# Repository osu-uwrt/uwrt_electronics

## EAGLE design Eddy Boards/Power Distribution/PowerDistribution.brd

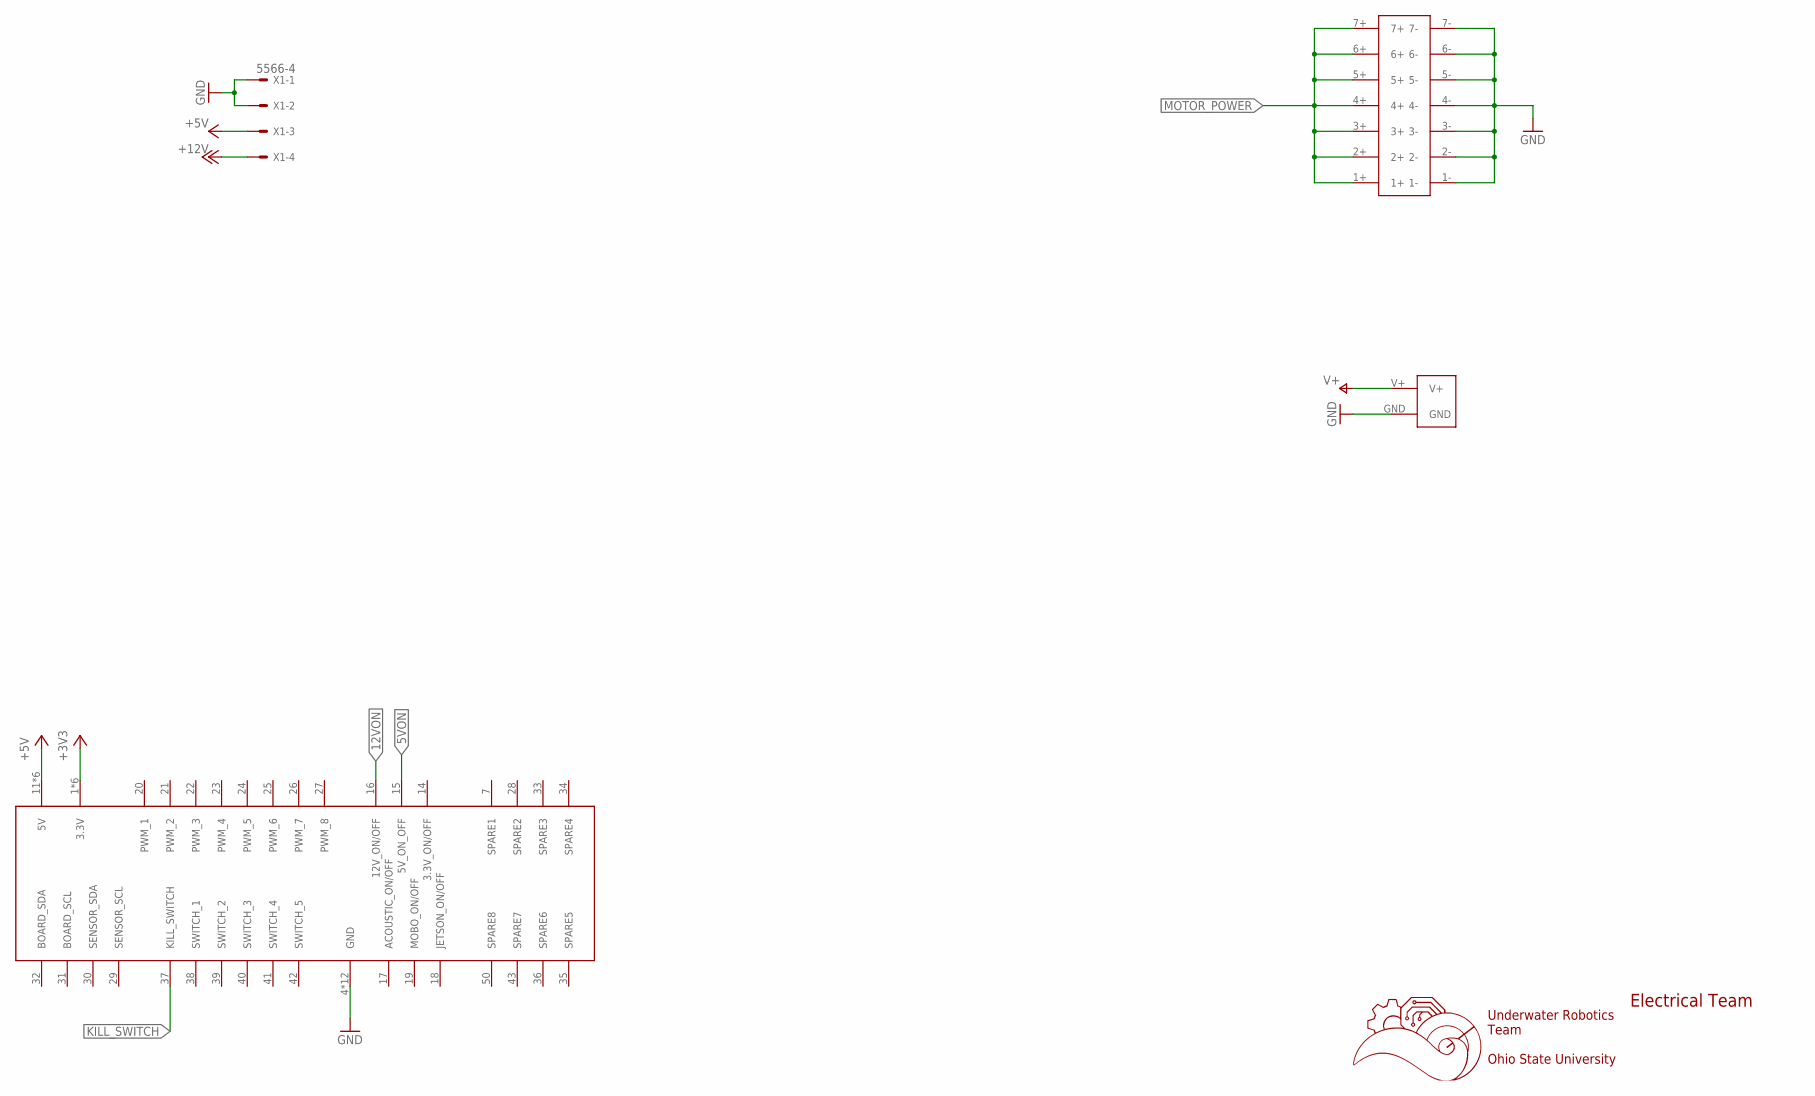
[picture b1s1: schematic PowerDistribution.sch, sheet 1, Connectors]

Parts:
U$1: 5530843-EDGE; 5530843-6-BOARDFINGERS
U$2: XT90PWH
U$4: 14PIN-VERT; 14PIN_VERT
X1: 5566-4

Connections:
5VON: U$1.15 (5V_ON_OFF); also elsewhere on the board
12VON: U$1.16 (12V_ON/OFF); also elsewhere on the board
+3V3: U$1.1 (3.3V), U$1.2 (3.3V), U$1.3 (3.3V), U$1.54 (3.3V), U$1.55 (3.3V), U$1.56 (3.3V); also elsewhere on the board
+5V: U$1.11 (5V), U$1.12 (5V), U$1.13 (5V), U$1.44 (5V), U$1.45 (5V), U$1.46 (5V), X1.3; also elsewhere on the board
+12V: X1.4; also elsewhere on the board
GND: U$1.4 (GND), U$1.5 (GND), U$1.6 (GND), U$1.8 (GND), U$1.9 (GND), U$1.10 (GND), U$1.47 (GND), U$1.48 (GND), U$1.49 (GND), U$1.51 (GND), U$1.52 (GND), U$1.53 (GND), U$2.GND, U$4.1-, U$4.2-, U$4.3-, U$4.4-, U$4.5-, U$4.6-, U$4.7-, X1.1, X1.2; also elsewhere on the board
KILL_SWITCH: U$1.37 (KILL_SWITCH); also elsewhere on the board
MOTOR_POWER: U$4.1+, U$4.2+, U$4.3+, U$4.4+, U$4.5+, U$4.6+, U$4.7+; also elsewhere on the board
V+: U$2.V+; also elsewhere on the board

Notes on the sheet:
Underwater Robotics Team Ohio State University
Electrical Team

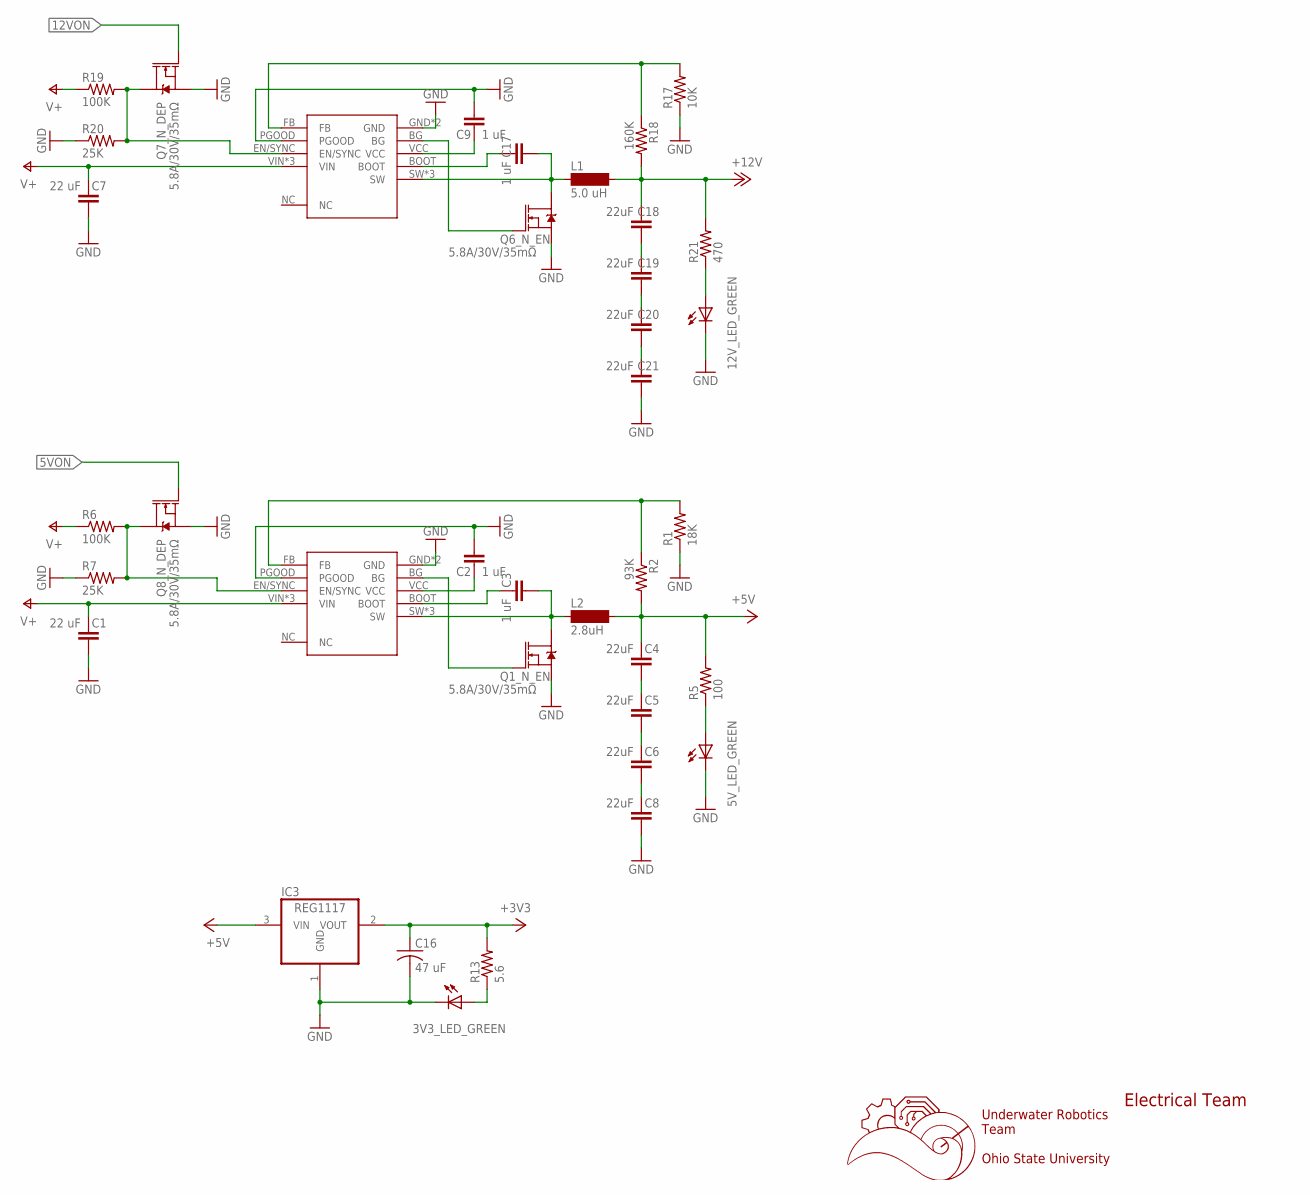
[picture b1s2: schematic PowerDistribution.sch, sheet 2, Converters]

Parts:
3V3_LED_GREEN, 5V_LED_GREEN, 12V_LED_GREEN: LEDCHIPLED_0603; CHIPLED_0603
C1, C7: 22 uF; C0603
C2, C3, C9, C17: 1 uF; C0603
C4, C5, C6, C8, C18, C19, C20, C21: 22uF; C0603
C16: 47 uF; C1206K
IC3: REG1117; SOT223
L1: 5.0 uH; MS85
L2: 2.8uH; MS85
Q1_N_EN, Q6_N_EN, Q7_N_DEP, Q8_N_DEP: 5.8A/30V/35mΩ; SOT23-3
R1: 18K; R0603
R2: 93K; R0603
R5: 100; R0603
R6, R19: 100K; R0603
R7, R20: 25K; R0603
R13: 5.6; R0603
R17: 10K; R0603
R18: 160K; R0603
R21: 470; R0603
U$3, U$6: RT7258-2

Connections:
5VEN: Q8_N_DEP.3 (D), R6.2, R7.2, U$3.EN/SYNC
5VON: Q8_N_DEP.1 (G); also elsewhere on the board
12EN: Q7_N_DEP.3 (D), R19.2, R20.2, U$6.EN/SYNC
12VON: Q7_N_DEP.1 (G); also elsewhere on the board
+3V3: C16.1, IC3.2 (VOUT), R13.2; also elsewhere on the board
+5V: C4.2, IC3.3 (VIN), L2.2, R2.2, R5.2; also elsewhere on the board
+12V: C18.2, L1.2, R18.2, R21.2; also elsewhere on the board
BG: Q1_N_EN.1 (G), U$3.BG
BG2: Q6_N_EN.1 (G), U$6.BG
GND: 3V3_LED_GREEN.C, 5V_LED_GREEN.C, 12V_LED_GREEN.C, C1.1, C2.1, C7.1, C8.1, C9.1, C16.2, C21.1, IC3.1 (GND), Q1_N_EN.2 (S), Q6_N_EN.2 (S), Q7_N_DEP.2 (S), Q8_N_DEP.2 (S), R1.1, R7.1, R17.1, R20.1, U$3.GND, U$3.GND2 (GND), U$3.PGOOD, U$6.GND, U$6.GND2 (GND), U$6.PGOOD; also elsewhere on the board
unnamed: C2.2, U$3.VCC
unnamed: C3.2, U$3.BOOT
unnamed: C5.1, C6.2
unnamed: C6.1, C8.2
unnamed: C4.1, C5.2
unnamed: R1.2, R2.1, U$3.FB
unnamed: 5V_LED_GREEN.A, R5.1
unnamed: C9.2, U$6.VCC
unnamed: 12V_LED_GREEN.A, R21.1
unnamed: C17.2, U$6.BOOT
unnamed: C19.1, C20.2
unnamed: C20.1, C21.2
unnamed: C18.1, C19.2
unnamed: R17.2, R18.1, U$6.FB
unnamed: 3V3_LED_GREEN.A, R13.1
V+: C1.2, C7.2, R6.1, R19.1, U$3.VIN, U$3.VIN2 (VIN), U$3.VIN3 (VIN), U$6.VIN, U$6.VIN2 (VIN), U$6.VIN3 (VIN); also elsewhere on the board
V+1: C17.1, L1.1, Q6_N_EN.3 (D), U$6.SW, U$6.SW2 (SW), U$6.SW3 (SW)
V+2: C3.1, L2.1, Q1_N_EN.3 (D), U$3.SW, U$3.SW2 (SW), U$3.SW3 (SW)

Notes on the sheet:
Underwater Robotics Team Ohio State University
Electrical Team

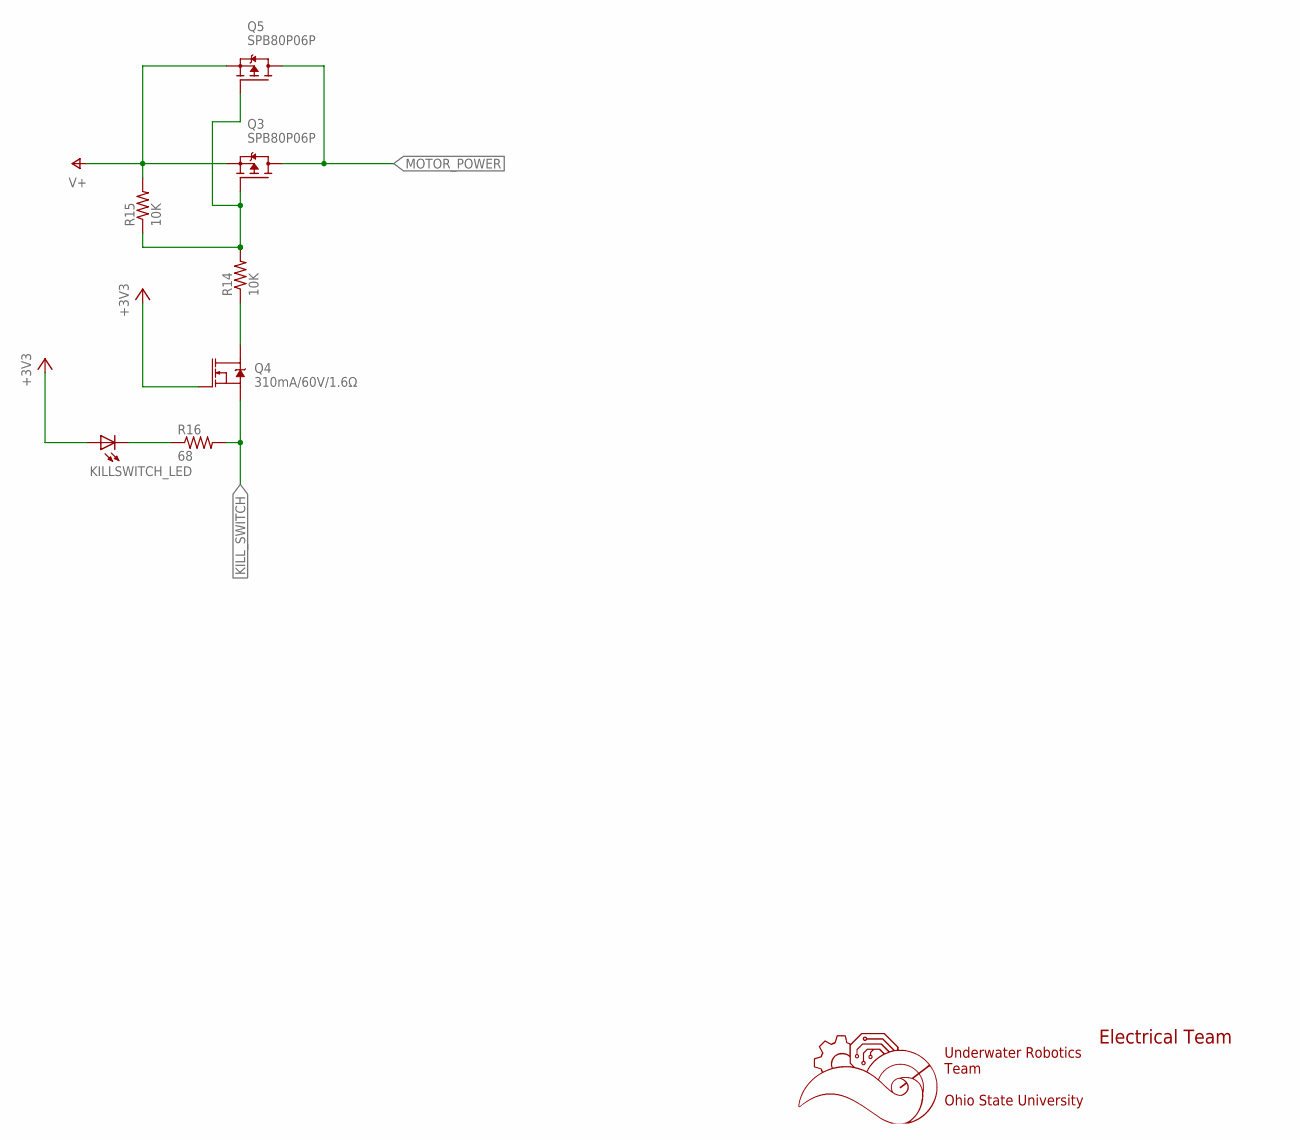
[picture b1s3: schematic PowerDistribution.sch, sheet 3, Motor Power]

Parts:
KILLSWITCH_LED: LEDCHIP-LED0603; CHIP-LED0603
Q3, Q5: SPB80P06P; TO263
Q4: 310mA/60V/1.6Ω; SOT323
R14, R15: 10K; R0603
R16: 68; R0603

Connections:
+3V3: KILLSWITCH_LED.A, Q4.1 (G); also elsewhere on the board
KILL_SWITCH: Q4.2 (S), R16.2; also elsewhere on the board
MOTOR_POWER: Q3.3 (D), Q5.3 (D); also elsewhere on the board
unnamed: Q4.3 (D), R14.1
unnamed: Q3.1 (G), Q5.1 (G), R14.2, R15.1
unnamed: KILLSWITCH_LED.C, R16.1
V+: Q3.2 (S), Q5.2 (S), R15.2; also elsewhere on the board

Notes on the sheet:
Underwater Robotics Team Ohio State University
Electrical Team

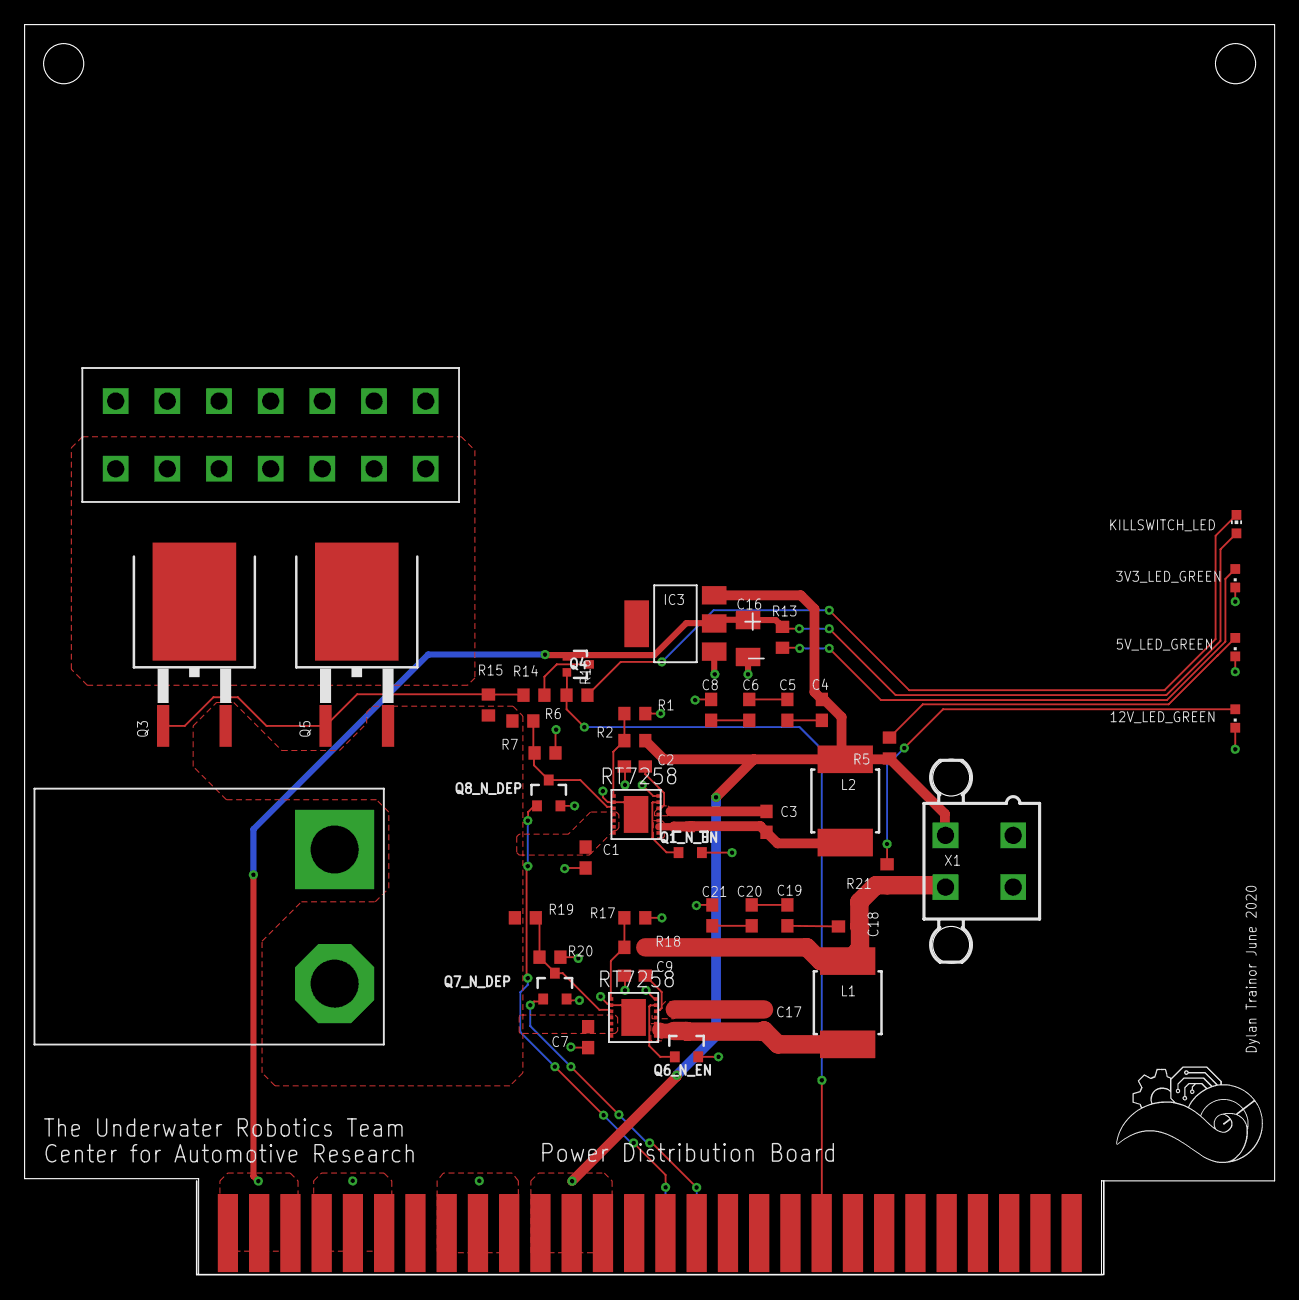
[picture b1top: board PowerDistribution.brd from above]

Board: 2 copper layers, 101.6 x 101.6 mm, 49 parts (0 on the bottom side), 33 nets.

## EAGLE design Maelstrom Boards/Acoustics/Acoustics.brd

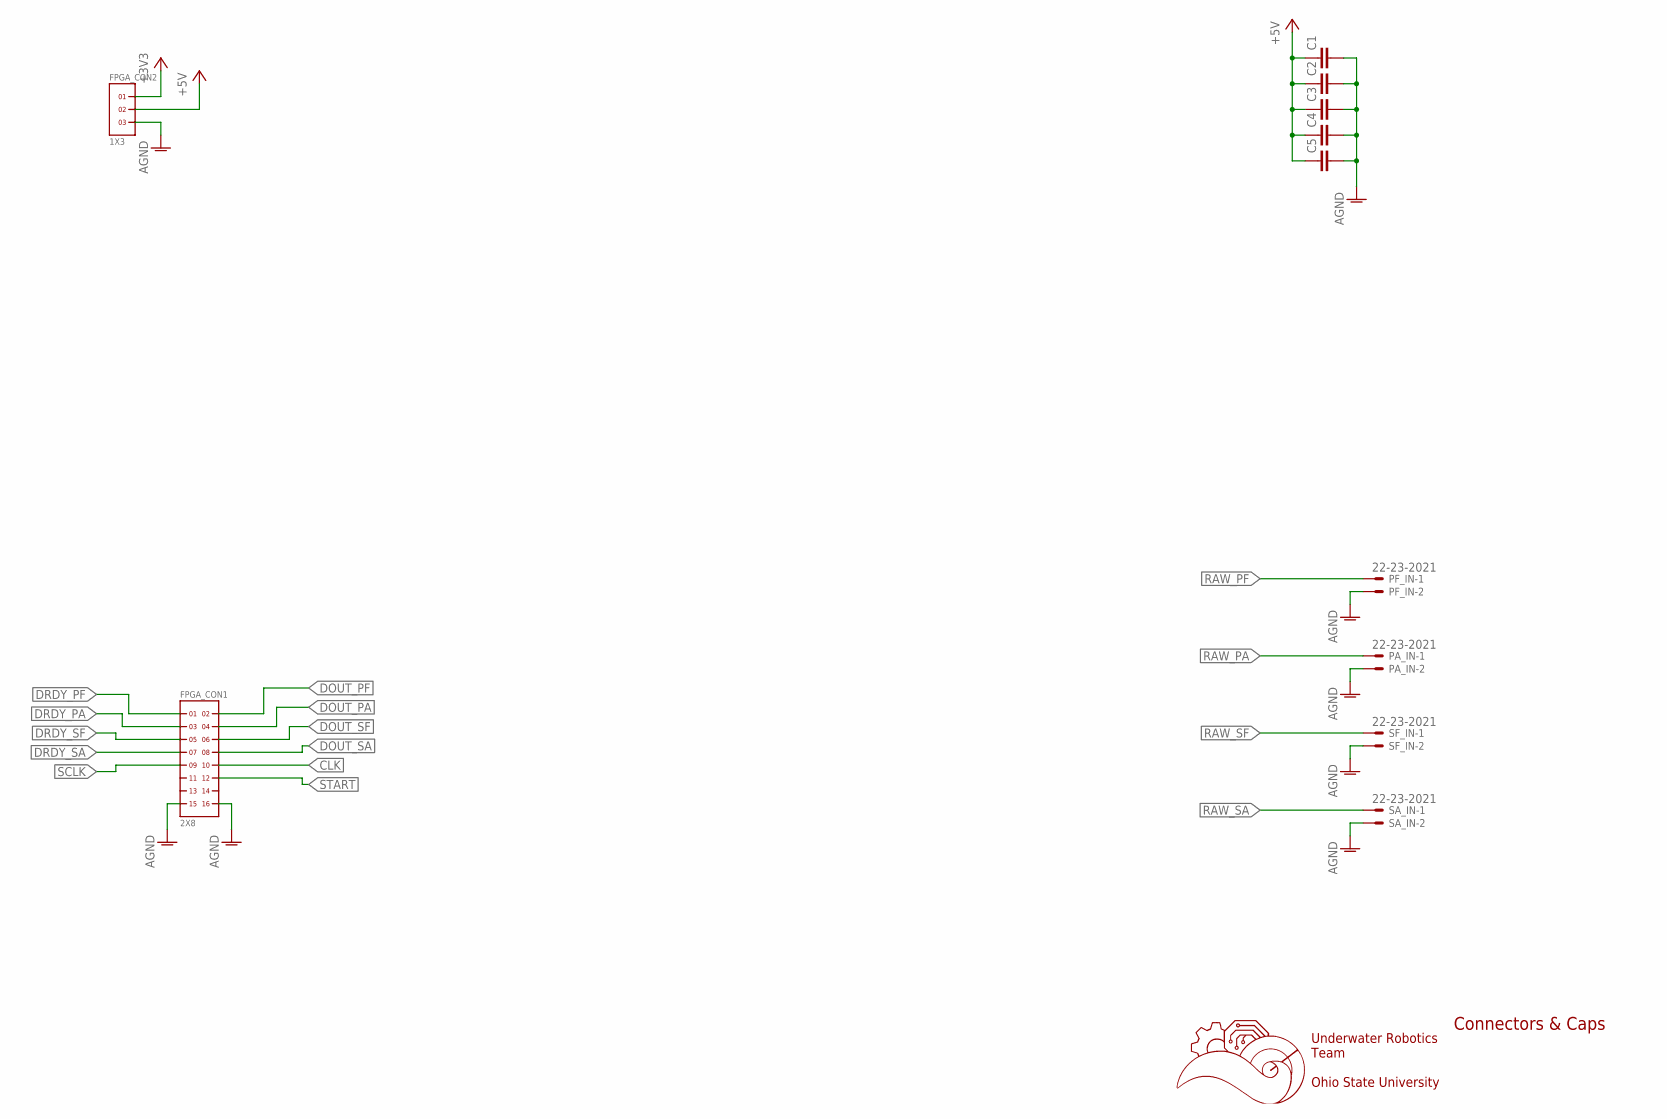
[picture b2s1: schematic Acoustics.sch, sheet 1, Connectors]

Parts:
C1, C2, C3, C4, C5: C2,5-3; C2.5-3
FPGA_CON1: 2X8
FPGA_CON2: 1X3
PA_IN: 22-23-2021
PF_IN: 22-23-2021
SA_IN: 22-23-2021
SF_IN: 22-23-2021

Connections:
+3V3: FPGA_CON2.1; also elsewhere on the board
+5V: C1.1, C2.1, C3.1, C4.1, C5.1, FPGA_CON2.2
CLK: FPGA_CON1.10; also elsewhere on the board
DOUT_PA: FPGA_CON1.4; also elsewhere on the board
DOUT_PF: FPGA_CON1.2; also elsewhere on the board
DOUT_SA: FPGA_CON1.8; also elsewhere on the board
DOUT_SF: FPGA_CON1.6; also elsewhere on the board
DRDY_PA: FPGA_CON1.3; also elsewhere on the board
DRDY_PF: FPGA_CON1.1; also elsewhere on the board
DRDY_SA: FPGA_CON1.7; also elsewhere on the board
DRDY_SF: FPGA_CON1.5; also elsewhere on the board
GND: C1.2, C2.2, C3.2, C4.2, C5.2, FPGA_CON1.15, FPGA_CON1.16, FPGA_CON2.3, PA_IN.2, PF_IN.2, SA_IN.2, SF_IN.2; also elsewhere on the board
RAW_PA: PA_IN.1; also elsewhere on the board
RAW_PF: PF_IN.1; also elsewhere on the board
RAW_SA: SA_IN.1; also elsewhere on the board
RAW_SF: SF_IN.1; also elsewhere on the board
SCLK: FPGA_CON1.9; also elsewhere on the board
START: FPGA_CON1.12; also elsewhere on the board

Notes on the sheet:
Underwater Robotics Team Ohio State University
Connectors & Caps

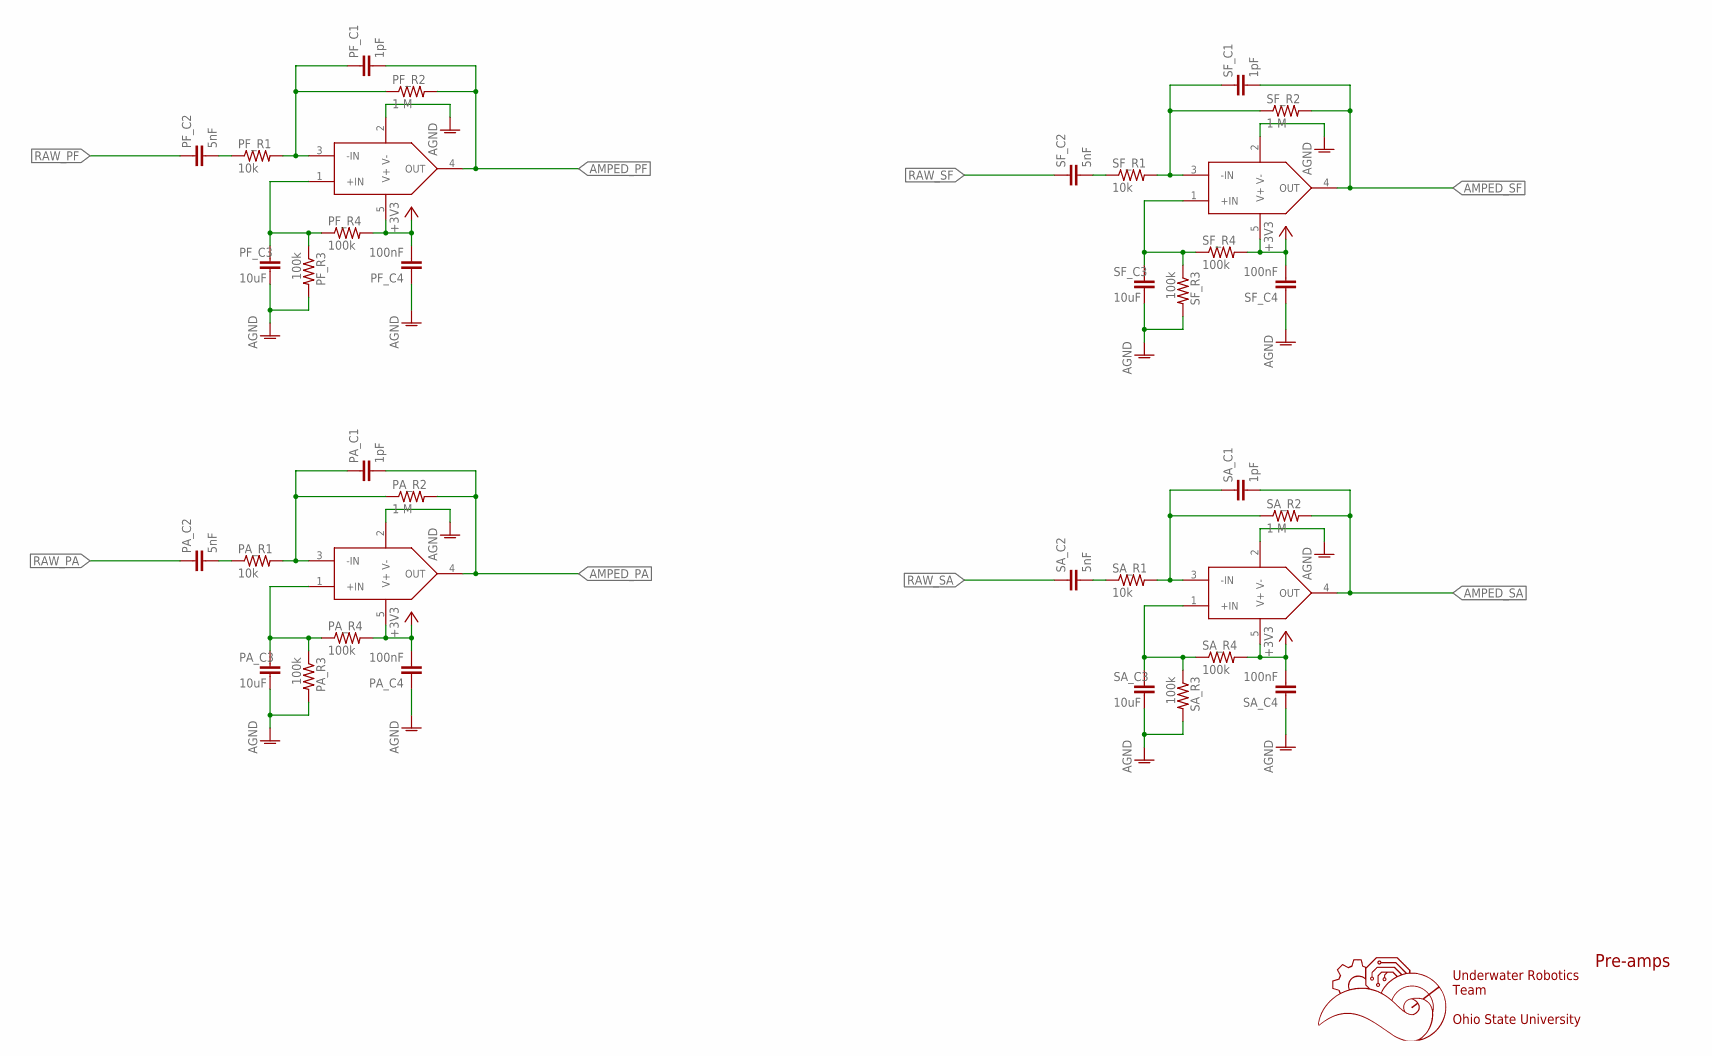
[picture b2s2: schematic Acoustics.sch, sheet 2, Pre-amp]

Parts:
H4_PREAMP4: TLV6741; SC70-5
PA_C1: 1pF; C0603
PA_C2: 5nF; C0603
PA_C3: 10uF; C0603
PA_C4: 100nF; C0603
PA_PREAMP: TLV6741; SC70-5
PA_R1: 10k; R0603
PA_R2: 1 M; R0603
PA_R3, PA_R4: 100k; R0603
PF_C1: 1pF; C0603
PF_C2: 5nF; C0603
PF_C3: 10uF; C0603
PF_C4: 100nF; C0603
PF_PREAMP: TLV6741; SC70-5
PF_R1: 10k; R0603
PF_R2: 1 M; R0603
PF_R3, PF_R4: 100k; R0603
SA_C1: 1pF; C0603
SA_C2: 5nF; C0603
SA_C3: 10uF; C0603
SA_C4: 100nF; C0603
SA_R1: 10k; R0603
SA_R2: 1 M; R0603
SA_R3, SA_R4: 100k; R0603
SF_C1: 1pF; C0603
SF_C2: 5nF; C0603
SF_C3: 10uF; C0603
SF_C4: 100nF; C0603
SF_PREAMP3: TLV6741; SC70-5
SF_R1: 10k; R0603
SF_R2: 1 M; R0603
SF_R3, SF_R4: 100k; R0603

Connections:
+3V3: H4_PREAMP4.5 (V+), PA_C4.2, PA_PREAMP.5 (V+), PA_R4.2, PF_C4.2, PF_PREAMP.5 (V+), PF_R4.2, SA_C4.2, SA_R4.2, SF_C4.2, SF_PREAMP3.5 (V+), SF_R4.2; also elsewhere on the board
AMPED_PA: PA_C1.2, PA_PREAMP.4 (OUT), PA_R2.2; also elsewhere on the board
AMPED_PF: PF_C1.2, PF_PREAMP.4 (OUT), PF_R2.2; also elsewhere on the board
AMPED_SA: H4_PREAMP4.4 (OUT), SA_C1.2, SA_R2.2; also elsewhere on the board
AMPED_SF: SF_C1.2, SF_PREAMP3.4 (OUT), SF_R2.2; also elsewhere on the board
GND: H4_PREAMP4.2 (V-), PA_C3.2, PA_C4.1, PA_PREAMP.2 (V-), PA_R3.2, PF_C3.2, PF_C4.1, PF_PREAMP.2 (V-), PF_R3.2, SA_C3.2, SA_C4.1, SA_R3.2, SF_C3.2, SF_C4.1, SF_PREAMP3.2 (V-), SF_R3.2; also elsewhere on the board
unnamed: PF_C2.2, PF_R1.1
unnamed: PF_C1.1, PF_PREAMP.3 (-IN), PF_R1.2, PF_R2.1
unnamed: PF_C3.1, PF_PREAMP.1 (+IN), PF_R3.1, PF_R4.1
unnamed: PA_C2.2, PA_R1.1
unnamed: PA_C1.1, PA_PREAMP.3 (-IN), PA_R1.2, PA_R2.1
unnamed: PA_C3.1, PA_PREAMP.1 (+IN), PA_R3.1, PA_R4.1
unnamed: SF_C2.2, SF_R1.1
unnamed: SF_C1.1, SF_PREAMP3.3 (-IN), SF_R1.2, SF_R2.1
unnamed: SF_C3.1, SF_PREAMP3.1 (+IN), SF_R3.1, SF_R4.1
unnamed: SA_C2.2, SA_R1.1
unnamed: H4_PREAMP4.3 (-IN), SA_C1.1, SA_R1.2, SA_R2.1
unnamed: H4_PREAMP4.1 (+IN), SA_C3.1, SA_R3.1, SA_R4.1
RAW_PA: PA_C2.1; also elsewhere on the board
RAW_PF: PF_C2.1; also elsewhere on the board
RAW_SA: SA_C2.1; also elsewhere on the board
RAW_SF: SF_C2.1; also elsewhere on the board

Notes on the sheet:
Underwater Robotics Team Ohio State University
Pre-amps

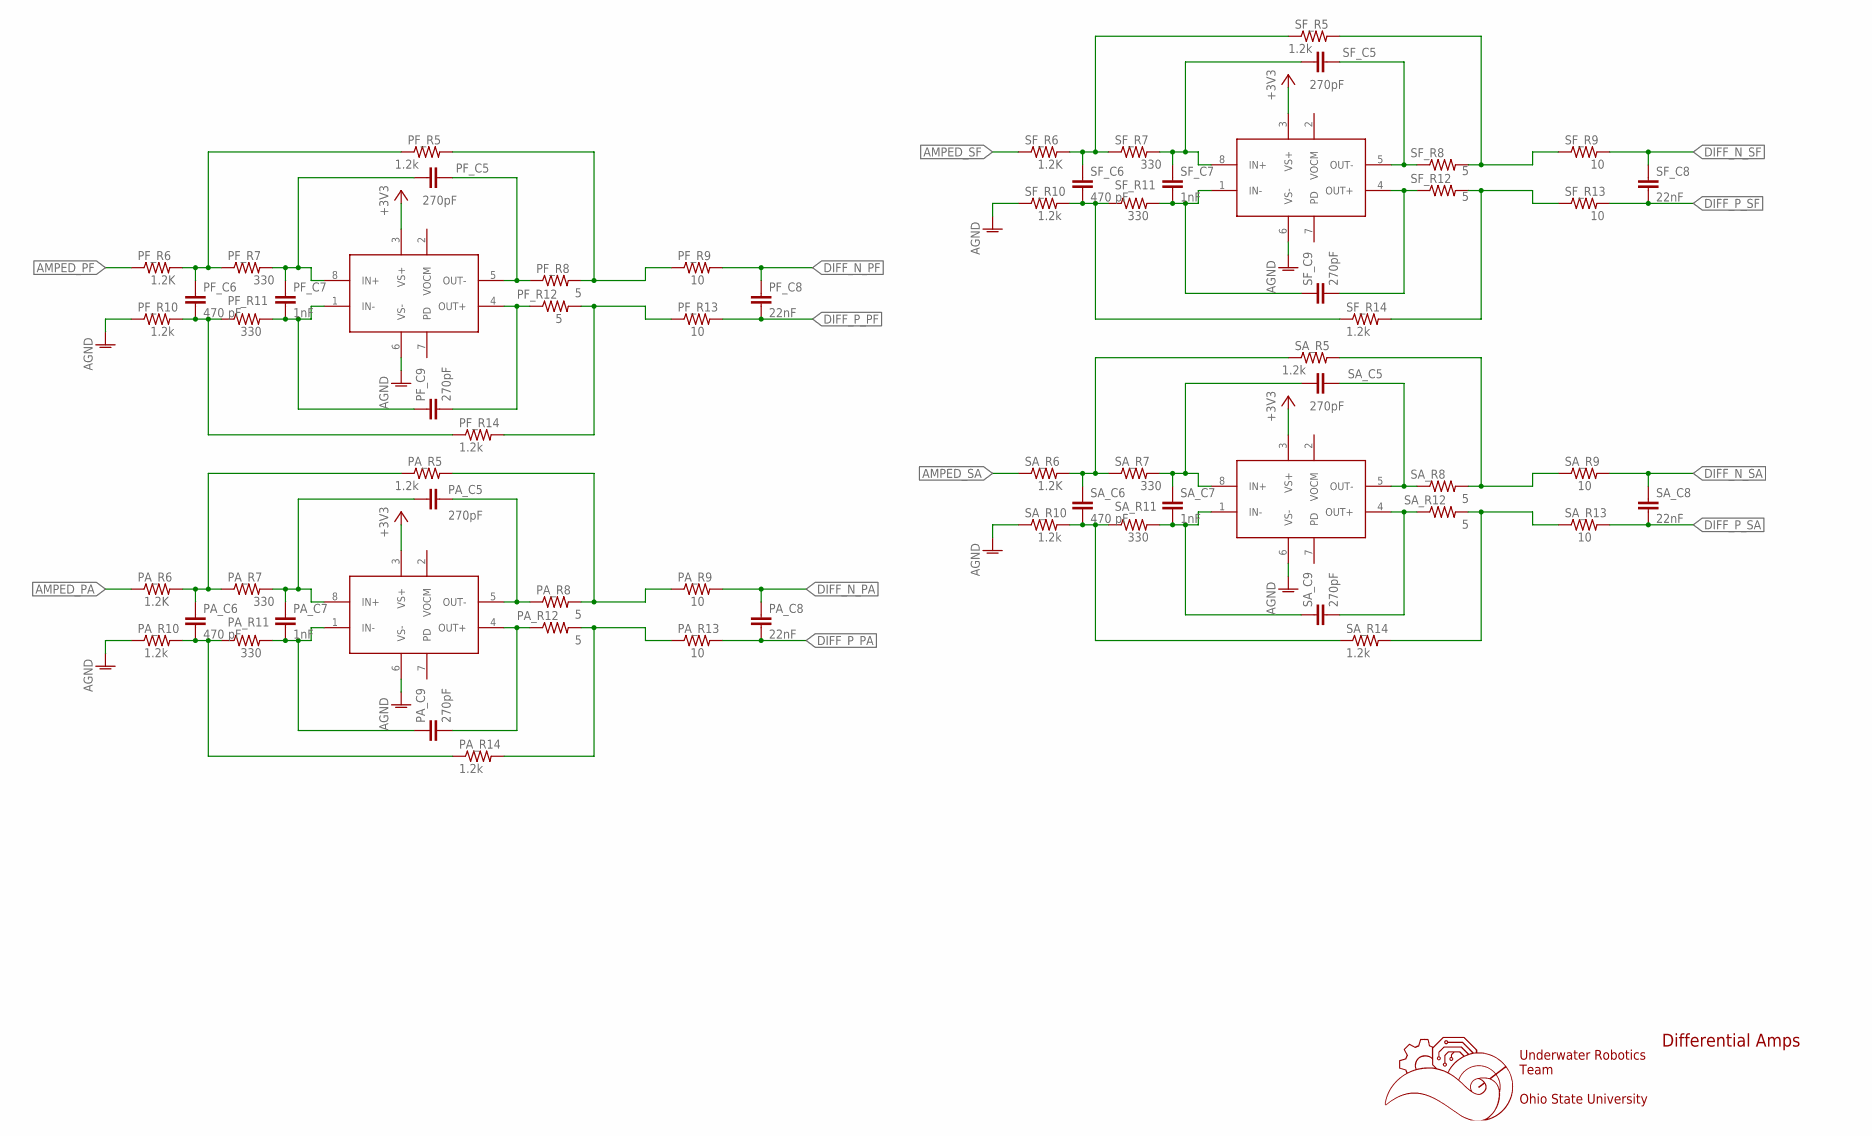
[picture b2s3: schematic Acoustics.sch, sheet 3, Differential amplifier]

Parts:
PA_C5, PA_C9: 270pF; C0603
PA_C6: 470 pF; C0603
PA_C7: 1nF; C0603
PA_C8: 22nF; C0603
PA_DA: THS4551; VSSOP-8
PA_R5, PA_R10, PA_R14: 1.2k; R0603
PA_R6: 1.2K; R0603
PA_R7, PA_R11: 330; R0603
PA_R8, PA_R12: 5; R0603
PA_R9, PA_R13: 10; R0603
PF_C5, PF_C9: 270pF; C0603
PF_C6: 470 pF; C0603
PF_C7: 1nF; C0603
PF_C8: 22nF; C0603
PF_DA: THS4551; VSSOP-8
PF_R5, PF_R10, PF_R14: 1.2k; R0603
PF_R6: 1.2K; R0603
PF_R7, PF_R11: 330; R0603
PF_R8, PF_R12: 5; R0603
PF_R9, PF_R13: 10; R0603
SA_C5, SA_C9: 270pF; C0603
SA_C6: 470 pF; C0603
SA_C7: 1nF; C0603
SA_C8: 22nF; C0603
SA_DA: THS4551; VSSOP-8
SA_R5, SA_R10, SA_R14: 1.2k; R0603
SA_R6: 1.2K; R0603
SA_R7, SA_R11: 330; R0603
SA_R8, SA_R12: 5; R0603
SA_R9, SA_R13: 10; R0603
SF_C5, SF_C9: 270pF; C0603
SF_C6: 470 pF; C0603
SF_C7: 1nF; C0603
SF_C8: 22nF; C0603
SF_DA: THS4551; VSSOP-8
SF_R5, SF_R10, SF_R14: 1.2k; R0603
SF_R6: 1.2K; R0603
SF_R7, SF_R11: 330; R0603
SF_R8, SF_R12: 5; R0603
SF_R9, SF_R13: 10; R0603

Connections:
+3V3: PA_DA.3 (VS+), PF_DA.3 (VS+), SA_DA.3 (VS+), SF_DA.3 (VS+); also elsewhere on the board
AMPED_PA: PA_R6.1; also elsewhere on the board
AMPED_PF: PF_R6.1; also elsewhere on the board
AMPED_SA: SA_R6.1; also elsewhere on the board
AMPED_SF: SF_R6.1; also elsewhere on the board
DIFF_N_PA: PA_C8.1, PA_R9.2; also elsewhere on the board
DIFF_N_PF: PF_C8.1, PF_R9.2; also elsewhere on the board
DIFF_N_SA: SA_C8.1, SA_R9.2; also elsewhere on the board
DIFF_N_SF: SF_C8.1, SF_R9.2; also elsewhere on the board
DIFF_P_PA: PA_C8.2, PA_R13.2; also elsewhere on the board
DIFF_P_PF: PF_C8.2, PF_R13.2; also elsewhere on the board
DIFF_P_SA: SA_C8.2, SA_R13.2; also elsewhere on the board
DIFF_P_SF: SF_C8.2, SF_R13.2; also elsewhere on the board
GND: PA_DA.6 (VS-), PA_R10.1, PF_DA.6 (VS-), PF_R10.1, SA_DA.6 (VS-), SA_R10.1, SF_DA.6 (VS-), SF_R10.1; also elsewhere on the board
unnamed: PA_C5.2, PA_DA.5 (OUT-), PA_R8.1
unnamed: PA_C5.1, PA_C7.1, PA_DA.8 (IN+), PA_R7.2
unnamed: PA_C7.2, PA_C9.1, PA_DA.1 (IN-), PA_R11.2
unnamed: PA_C6.1, PA_R5.1, PA_R6.2, PA_R7.1
unnamed: PA_C6.2, PA_R10.2, PA_R11.1, PA_R14.1
unnamed: PA_C9.2, PA_DA.4 (OUT+), PA_R12.1
unnamed: PA_R5.2, PA_R8.2, PA_R9.1
unnamed: PA_R12.2, PA_R13.1, PA_R14.2
unnamed: SF_C5.2, SF_DA.5 (OUT-), SF_R8.1
unnamed: SF_C5.1, SF_C7.1, SF_DA.8 (IN+), SF_R7.2
unnamed: SF_C7.2, SF_C9.1, SF_DA.1 (IN-), SF_R11.2
unnamed: SF_C6.1, SF_R5.1, SF_R6.2, SF_R7.1
unnamed: SF_C6.2, SF_R10.2, SF_R11.1, SF_R14.1
unnamed: SF_C9.2, SF_DA.4 (OUT+), SF_R12.1
unnamed: SF_R5.2, SF_R8.2, SF_R9.1
unnamed: SF_R12.2, SF_R13.1, SF_R14.2
unnamed: SA_C5.2, SA_DA.5 (OUT-), SA_R8.1
unnamed: SA_C5.1, SA_C7.1, SA_DA.8 (IN+), SA_R7.2
unnamed: SA_C7.2, SA_C9.1, SA_DA.1 (IN-), SA_R11.2
unnamed: SA_C6.1, SA_R5.1, SA_R6.2, SA_R7.1
unnamed: SA_C6.2, SA_R10.2, SA_R11.1, SA_R14.1
unnamed: SA_C9.2, SA_DA.4 (OUT+), SA_R12.1
unnamed: SA_R5.2, SA_R8.2, SA_R9.1
unnamed: SA_R12.2, SA_R13.1, SA_R14.2
unnamed: PF_R12.2, PF_R13.1, PF_R14.2
unnamed: PF_C5.2, PF_DA.5 (OUT-), PF_R8.1
unnamed: PF_C5.1, PF_C7.1, PF_DA.8 (IN+), PF_R7.2
unnamed: PF_C7.2, PF_C9.1, PF_DA.1 (IN-), PF_R11.2
unnamed: PF_C6.1, PF_R5.1, PF_R6.2, PF_R7.1
unnamed: PF_C6.2, PF_R10.2, PF_R11.1, PF_R14.1
unnamed: PF_C9.2, PF_DA.4 (OUT+), PF_R12.1
unnamed: PF_R5.2, PF_R8.2, PF_R9.1

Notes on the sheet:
Underwater Robotics Team Ohio State University
Differential Amps

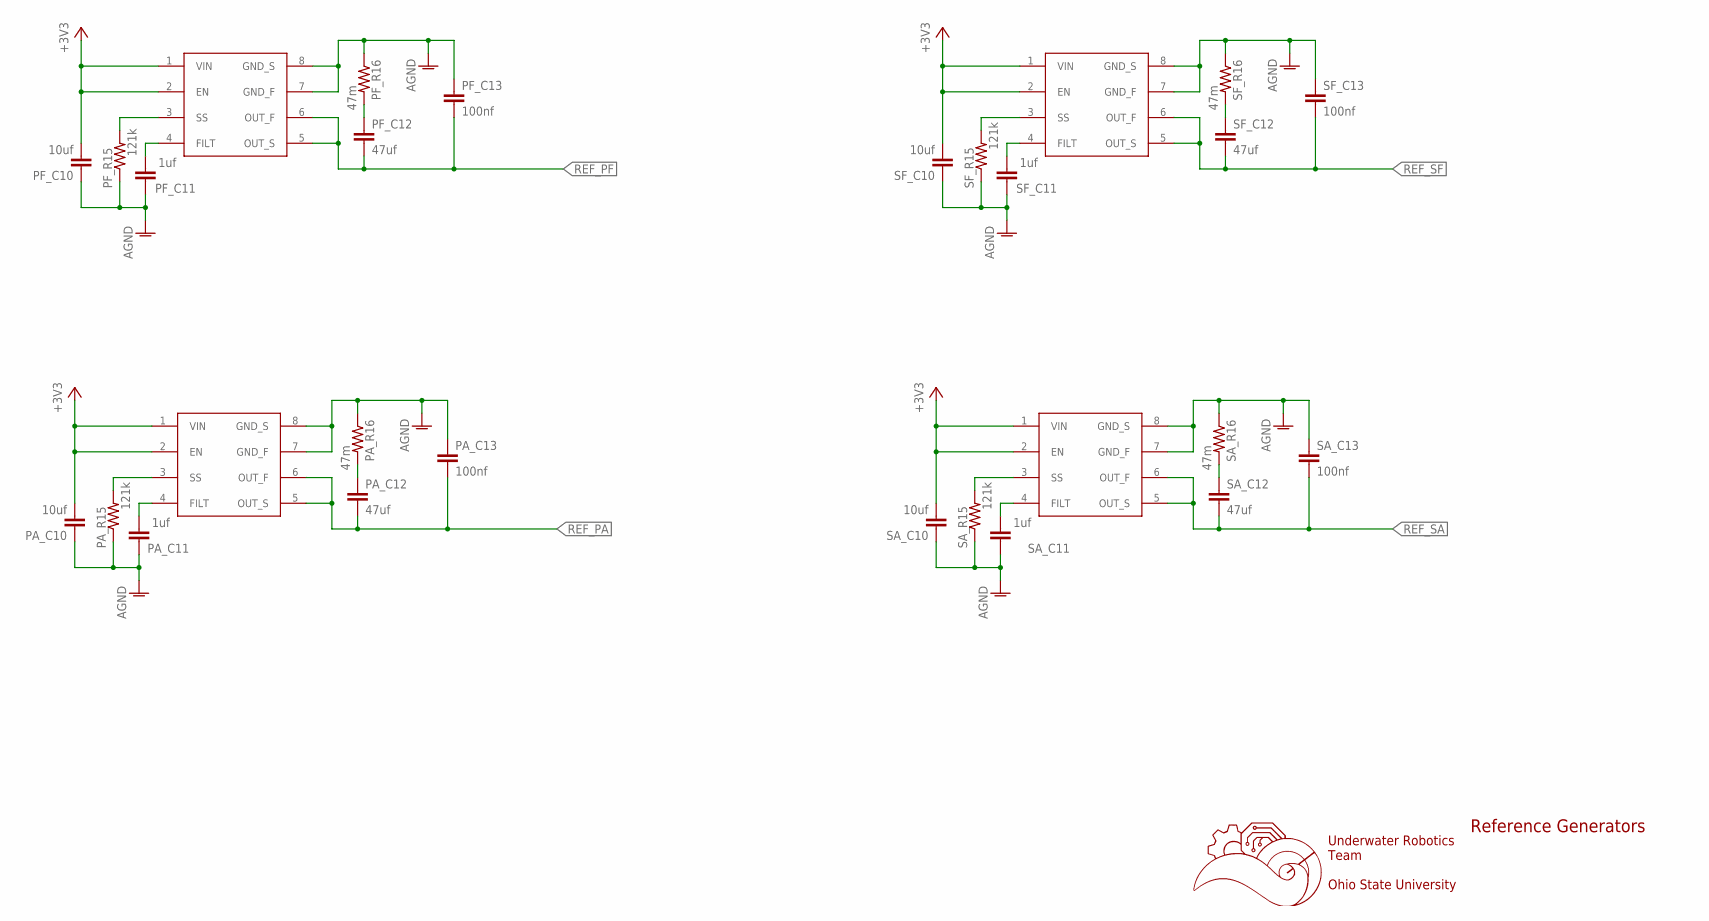
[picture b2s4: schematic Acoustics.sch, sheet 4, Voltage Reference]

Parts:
PA_C10: 10uf; C0603
PA_C11: 1uf; C0603
PA_C12: 47uf; C0603
PA_C13: 100nf; C0603
PA_R15: 121k; R0603
PA_R16: 47m; R0603
PA_REFGEN: REF6025
PF_C10: 10uf; C0603
PF_C11: 1uf; C0603
PF_C12: 47uf; C0603
PF_C13: 100nf; C0603
PF_R15: 121k; R0603
PF_R16: 47m; R0603
PF_REFGEN: REF6025
SA_C10: 10uf; C0603
SA_C11: 1uf; C0603
SA_C12: 47uf; C0603
SA_C13: 100nf; C0603
SA_R15: 121k; R0603
SA_R16: 47m; R0603
SA_REFGEN: REF6025
SF_C10: 10uf; C0603
SF_C11: 1uf; C0603
SF_C12: 47uf; C0603
SF_C13: 100nf; C0603
SF_R15: 121k; R0603
SF_R16: 47m; R0603
SF_REFGEN: REF6025

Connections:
+3V3: PA_C10.2, PA_REFGEN.1 (VIN), PA_REFGEN.2 (EN), PF_C10.2, PF_REFGEN.1 (VIN), PF_REFGEN.2 (EN), SA_C10.2, SA_REFGEN.1 (VIN), SA_REFGEN.2 (EN), SF_C10.2, SF_REFGEN.1 (VIN), SF_REFGEN.2 (EN); also elsewhere on the board
GND: PA_C10.1, PA_C11.1, PA_C13.1, PA_R15.1, PA_R16.1, PA_REFGEN.7 (GND_F), PA_REFGEN.8 (GND_S), PF_C10.1, PF_C11.1, PF_C13.1, PF_R15.1, PF_R16.1, PF_REFGEN.7 (GND_F), PF_REFGEN.8 (GND_S), SA_C10.1, SA_C11.1, SA_C13.1, SA_R15.1, SA_R16.1, SA_REFGEN.7 (GND_F), SA_REFGEN.8 (GND_S), SF_C10.1, SF_C11.1, SF_C13.1, SF_R15.1, SF_R16.1, SF_REFGEN.7 (GND_F), SF_REFGEN.8 (GND_S); also elsewhere on the board
unnamed: PF_C11.2, PF_REFGEN.4 (FILT)
unnamed: PF_R15.2, PF_REFGEN.3 (SS)
unnamed: PF_C12.1, PF_R16.2
unnamed: PA_C11.2, PA_REFGEN.4 (FILT)
unnamed: PA_R15.2, PA_REFGEN.3 (SS)
unnamed: PA_C12.1, PA_R16.2
unnamed: SF_C11.2, SF_REFGEN.4 (FILT)
unnamed: SF_R15.2, SF_REFGEN.3 (SS)
unnamed: SF_C12.1, SF_R16.2
unnamed: SA_C11.2, SA_REFGEN.4 (FILT)
unnamed: SA_R15.2, SA_REFGEN.3 (SS)
unnamed: SA_C12.1, SA_R16.2
REF_PA: PA_C12.2, PA_C13.2, PA_REFGEN.5 (OUT_S), PA_REFGEN.6 (OUT_F); also elsewhere on the board
REF_PF: PF_C12.2, PF_C13.2, PF_REFGEN.5 (OUT_S), PF_REFGEN.6 (OUT_F); also elsewhere on the board
REF_SA: SA_C12.2, SA_C13.2, SA_REFGEN.5 (OUT_S), SA_REFGEN.6 (OUT_F); also elsewhere on the board
REF_SF: SF_C12.2, SF_C13.2, SF_REFGEN.5 (OUT_S), SF_REFGEN.6 (OUT_F); also elsewhere on the board

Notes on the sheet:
Underwater Robotics Team Ohio State University
Reference Generators

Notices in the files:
parts and their libraries:
SparkFun-DiscreteSemi: Licensing: Creative Commons ShareAlike 4.0 International - https://creativecommons.org/licenses/by-sa/4.0
con-molex-mini-fit: Copyright (C) 2011, Bob Starr
